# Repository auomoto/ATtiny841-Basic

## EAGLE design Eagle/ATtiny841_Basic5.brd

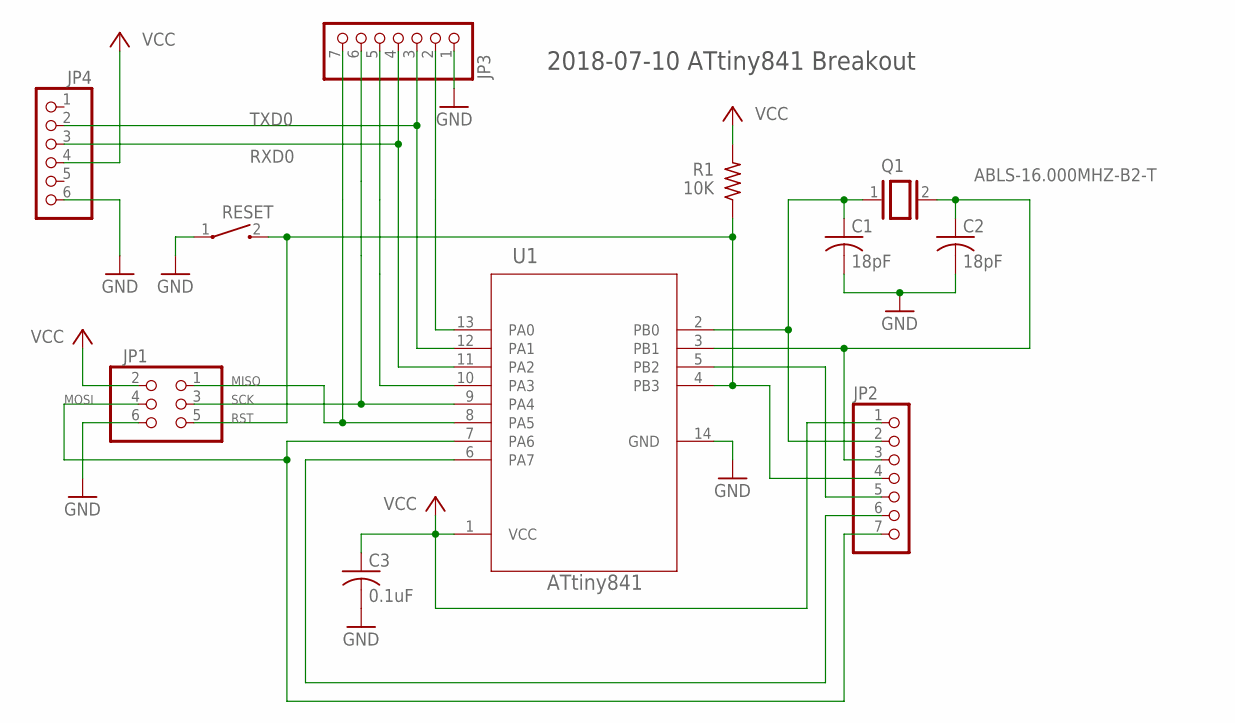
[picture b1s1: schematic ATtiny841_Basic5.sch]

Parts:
C1, C2: 18pF; C0805
C3: 0.1uF; C0805
JP1: PINHD-2X3; 2X03
JP2, JP3: PINHD-1X7; 1X07
JP4: PINHD-1X6/90; 1X06/90
Q1: ABLS-16.000MHZ-B2-T; XTAL1140X470X420
R1: 10K; R0805
RESET: SPST-THROUGHHOLE
U1: ATtiny841; SOIC127P599X175-14

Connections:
GND: C1.2, C2.2, C3.2, JP1.6, JP3.1, JP4.6, RESET.1, U1.14 (GND)
MISO: JP1.1, JP3.7, U1.8 (PA5)
MOSI: JP1.4, JP2.7, U1.7 (PA6)
PA0: JP3.2, U1.13 (PA0)
PA3: JP3.5, U1.10 (PA3)
PA7: JP2.6, U1.6 (PA7)
PB0: C1.1, JP2.2, Q1.1, U1.2 (PB0)
PB1: C2.1, JP2.3, Q1.2, U1.3 (PB1)
PB2: JP2.5, U1.5 (PB2)
RST: JP1.5, JP2.4, R1.1, RESET.2, U1.4 (PB3)
RXD0: JP3.4, JP4.3, U1.11 (PA2)
SCK: JP1.3, JP3.6, U1.9 (PA4)
TXD0: JP3.3, JP4.2, U1.12 (PA1)
VCC: C3.1, JP1.2, JP2.1, JP4.4, R1.2, U1.1 (VCC)

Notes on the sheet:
2018-07-10 ATtiny841 Breakout

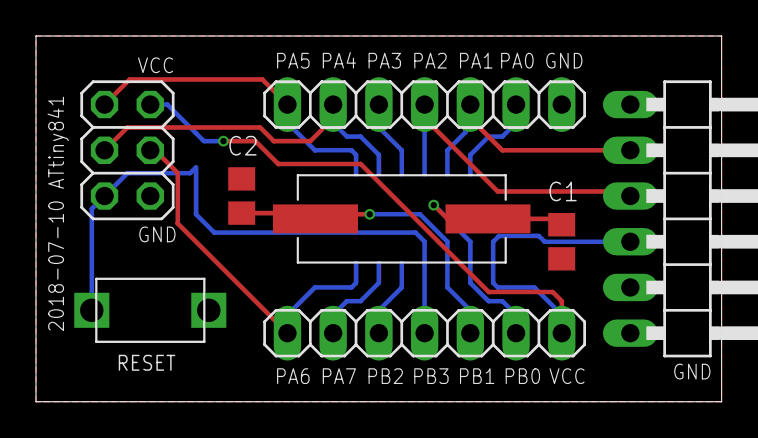
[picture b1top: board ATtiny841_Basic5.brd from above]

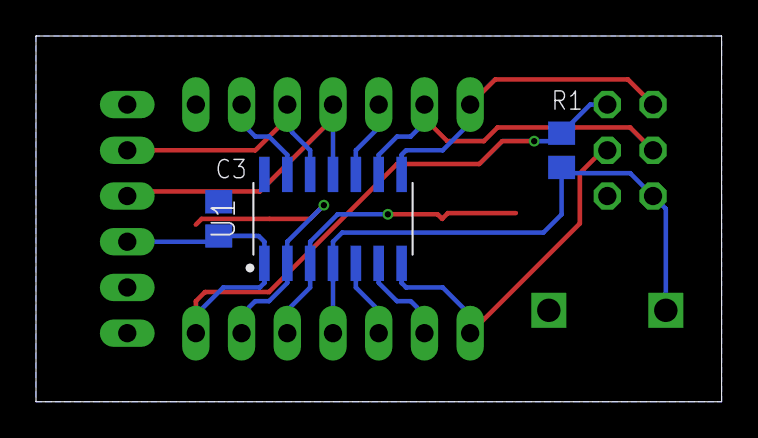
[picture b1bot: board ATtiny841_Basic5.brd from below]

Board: 2 copper layers, 38.1 x 20.3 mm, 11 parts (3 on the bottom side), 14 nets.

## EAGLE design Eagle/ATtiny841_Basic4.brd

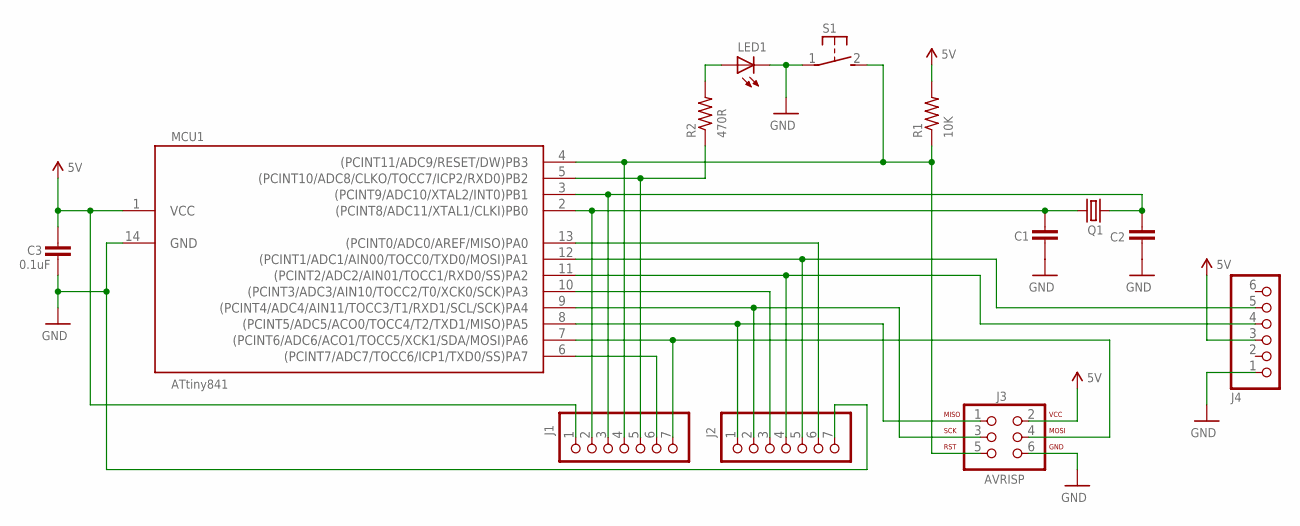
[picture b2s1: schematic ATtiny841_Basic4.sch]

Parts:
C1, C2: C-UNPOL; CAP-PTH-SMALL2
C3: 0.1uF; CAP-PTH-SMALL2
J1, J2: PINHD-1X71X07-CLEANBIG; 1X07-CLEANBIG
J3: AVRISP; 2X03-CLEAN
J4: PINHD-1X6CB; 1X06-CLEANBIG
LED1: LED5MM
MCU1: ATtiny841; SOIC14
Q1: CRYSTALHC49S; HC49/S
R1: 10K; RESISTOR-0207/2V
R2: 470R; RESISTOR-0207/2V
S1: SW-SPST-TACT; DTS-3

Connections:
5V: C3.1, J1.1, J3.2, J4.3, MCU1.1 (VCC), R1.2
GND: C1.2, C2.1, C3.2, J2.7, J3.6, J4.1, LED1.K (C), MCU1.14 (GND), S1.1
MISO: J2.1, J3.1, MCU1.8 ((PCINT5/ADC5/ACO0/TOCC4/T2/TXD1/MISO)PA5)
MOSI: J1.7, J3.4, MCU1.7 ((PCINT6/ADC6/ACO1/TOCC5/XCK1/SDA/MOSI)P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)
unnamed: J1.6, MCU1.6 ((PCINT7/ADC7/TOCC6/ICP1/TXD0/SS)PA7)
unnamed: C1.1, J1.2, MCU1.2 ((PCINT8/ADC11/XTAL1/CLKI)PB0), Q1.1
unnamed: C2.2, J1.3, MCU1.3 ((PCINT9/ADC10/XTAL2/INT0)PB1), Q1.2
unnamed: J2.6, MCU1.13 ((PCINT0/ADC0/AREF/MISO)PA0)
unnamed: J2.3, MCU1.10 ((PCINT3/ADC3/AIN10/TOCC2/T0/XCK0/SCK)PA3)
unnamed: J1.5, MCU1.5 ((PCINT10/ADC8/CLKO/TOCC7/ICP2/RXD0)PB2), R2.1
unnamed: LED1.A, R2.2
RST: J1.4, J3.5, MCU1.4 ((PCINT11/ADC9/RESET/DW)PB3), R1.1, S1.2
RTS: J2.5, J4.5, MCU1.12 ((PCINT1/ADC1/AIN00/TOCC0/TXD0/MOSI)PA1)
RXD0: J2.4, J4.4, MCU1.11 ((PCINT2/ADC2/AIN01/TOCC1/RXD0/SS)PA2)
SCK: J2.2, J3.3, MCU1.9 ((PCINT4/ADC4/AIN11/TOCC3/T1/RXD1/SCL/SC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)

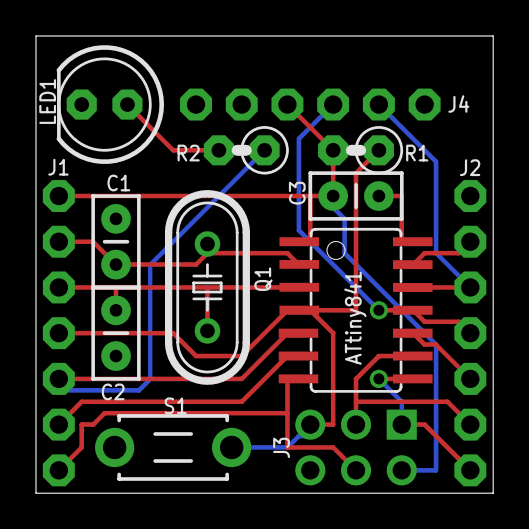
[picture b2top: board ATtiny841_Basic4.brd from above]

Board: 2 copper layers, 25.4 x 25.4 mm, 13 parts (0 on the bottom side), 15 nets.

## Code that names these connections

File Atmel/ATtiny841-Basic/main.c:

/*
 * ATtiny841_Basic.c
 *
 * Created: 2/15/2015 5:50:42 AM
 *  Author: Alan Uomoto

FUSES
Reading the fuses:
	avrdude -c usbtiny -p attiny841 -U lfuse:r:-:h

For an unmodified ATtiny841, this gives:
	lfuse = 0x42
	hfuse = 0xdf
	efuse = 0xff

We noticed that the lfuse value listed as default in the datasheet
(p 219) is 0x62. Bit 5, which is not used, is programmed (value = 0)
on my device but the datasheet says it's not (value = 1).

CLOCK SPEED 8 MHz

The factory default divides the internal clock by 8, resulting in a
1 MHz clock speed. I changed this so that the chip runs at 8 MHz (no
clock division) by changing lfuse to 0xC2.
	avrdude -c usbtiny -p attiny841 -U lfuse:w:0xC2:m
so:
	lfuse = 0xc2
	hfuse = 0xdf
	efuse = 0xff

CLOCK SPEED 14.745600 MHz

To use a 14.745600 MHz crystal, change the CKSEL[3:0] bits (p 26 & p 220)
to 111X.

So lfuse becomes 0xce:

avrdude -c usbtiny -p attiny841 -U lfuse:w:0xCE:m

USART
There are two:
	USART0: RXD0 is PA2 on pin 11, TXD0 is PA1 on pin 12
	USART1: RXD1 is PA4 on pin 9, TXD1 is PA5 on pin 8

 */ 

#define F_CPU 14745600

#include <avr/io.h>
#include <util/delay.h>

#define BAUDRATE	9600
#define MYUBRR		((F_CPU / 16 / BAUDRATE) - 1)
#define TX0READY	(UCSR0A & (1 << UDRE0))
#define TX1READY	(UCSR1A & (1 << UDRE1))

// Function prototypes
void flashLED(uint8_t);
void initialize(void);
void serial0SendByte(uint8_t);
void serial1SendByte(uint8_t);

int main(void)
{

	initialize();

	for (;;) {
		serial0SendByte('a');
		_delay_ms(1000);
	}

}

void initialize()
{

	// Setup serial port 0
	UBRR0H = (uint8_t) (MYUBRR >> 8);		// Set the baud rate
	UBRR0L = (uint8_t) MYUBRR;				// Set the baud rate (second half)
	UCSR0B = (1 << RXEN0) | (1 << TXEN0);	// Enable USART receive and transmit
	UCSR0C = (3 << UCSZ00);					// 8 bits, no parity, one stop bit

	// Setup serial port 1
	UBRR1H = (uint8_t) (MYUBRR >> 8);		// Set the baud rate
	UBRR1L = (uint8_t) MYUBRR;				// Set the baud rate (second half)
	UCSR1B = (1 << RXEN0) | (1 << TXEN0);	// Enable USART receive and transmit
	UCSR1C = (3 << UCSZ00);					// 8 bits, no parity, one stop bit

	// Set up the LED on the ATtiny841 Basic board
	DDRB |= (1 << PORTB2);					// LED is on PORTB2

	flashLED(5);

}

void flashLED(uint8_t ntimes)
{

	uint8_t i;

	for (i = 0; i < ntimes; i++) {
		PORTB |= (1 << PORTB2);
		_delay_ms(125);
		PORTB &= ~(1 << PORTB2);
		_delay_ms(125);
	}

}

void serial0SendByte(uint8_t c)
{

	while (!TX0READY) {
		asm("nop");
	}
	UDR0 = c;

}

void serial1SendByte(uint8_t c)
{

	while (!TX1READY) {
		asm("nop");
	}
	UDR1 = c;

}

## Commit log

2016-01-07 Serial0 testing
2018-07-22 New version, starting over
2018-07-22 Added to work laptop
